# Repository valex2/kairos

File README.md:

# Kairos
The objective of this project was to develop a low-cost, portable AQI (Air Quality Index) monitor that logs key air quality metrics and stores them for long-term tracking.

This is driven by the worsening air quality due to climate change, particularly in regions like California where wildfires contribute to increased particulate matter in the atmosphere. Affordable sensors, such as Kairos, offer a scalable solution for monitoring air quality across large areas, providing national agencies with valuable data to analyze climate patterns, identify hotspots, and allocate resources more effectively.

A key advantage of Kairos is its portability and accessibility. Designed to be carried by individuals, it requires minimal infrastructure, reducing the overhead costs typically associated with large-scale environmental monitoring. This enables on-the-ground data collection and empowers individuals to better understand and respond to the air quality and environmental hazards in their immediate surroundings, while also meaningfully contributing to a larger, community or state-wide, AQI dataset. This version of Kairos serves as a proof of concept and has the following features:

1. Embedded compute
    1. The [**ATMEL SAMD51J19**](https://www.microchip.com/en-us/product/atsamd51j19a), an accessible chip, with 120MHz CPU, 256 KB RAM, and plenty of IO buses to handle sensor data and logging.
2. Instrumentation
    1. A [**Bosch SensorTech BME 688**](https://www.bosch-sensortec.com/products/environmental-sensors/gas-sensors/bme688/) — enabling high-accuracy pressure, humidity, temperature, Volatile Organic Compound (VOC) and Volatile Sulfur Compound (VSC) monitoring.
    2. An [**LTR-329ALS-01**](https://www.mouser.com/datasheet/2/239/Lite-On_LTR-329ALS-01%20DS_ver1.1-348647.pdf) — enabling visible- and IR-range light intensity measurements.
3. Communication modalities
    1. A **USB bus** — for communication with a host computer
    2. A **microSD** bus — for time-stamped ***logging*** of sensor values. Using an external SD card allows for prolonged operation without needing to pause logging
    3. A **display** — for on the go monitoring of sensor values
4. Two different power modes
    1. **USB Power** — embedded voltage regulators enable Kairos to be used in a stationary setting, say a roof of a building, for extended periods of time
    2. **Battery Power** — a 2500mAh LiPO and embedded charging circuitry allow Kairos to be taken on the go, for better-monitoring frequently travelled environments without requiring frequent charging.

While this version of Kairos demonstrates proof of concept, future iterations should expand its capabilities with the following features:

1. **UV Sensor**: To capture sun intensity across more (and more dangerous) wavelengths, providing a more comprehensive solar exposure assessment.
2. **GPS Module**: To enable precise tracking of Kairos’ location, facilitating the creation of accurate heatmaps for key AQI metrics.
3. **Bluetooth Syncing**: To allow seamless data transfer to mobile phones, removing the need to manually retrieve data from an SD card.
4. **A Centralized Server**: To aggregate data from multiple Kairos units, generating regional-level heatmaps and providing actionable insights from averaged data points across different areas.
5. **A rugged, waterproof, miniaturized shell for on the go use.**

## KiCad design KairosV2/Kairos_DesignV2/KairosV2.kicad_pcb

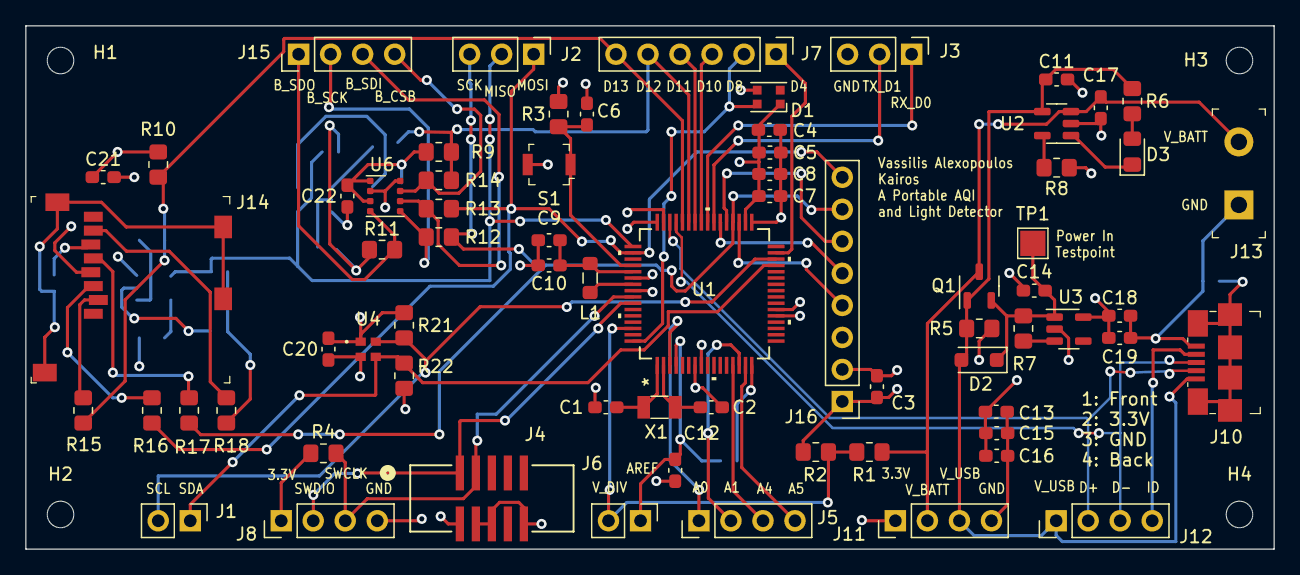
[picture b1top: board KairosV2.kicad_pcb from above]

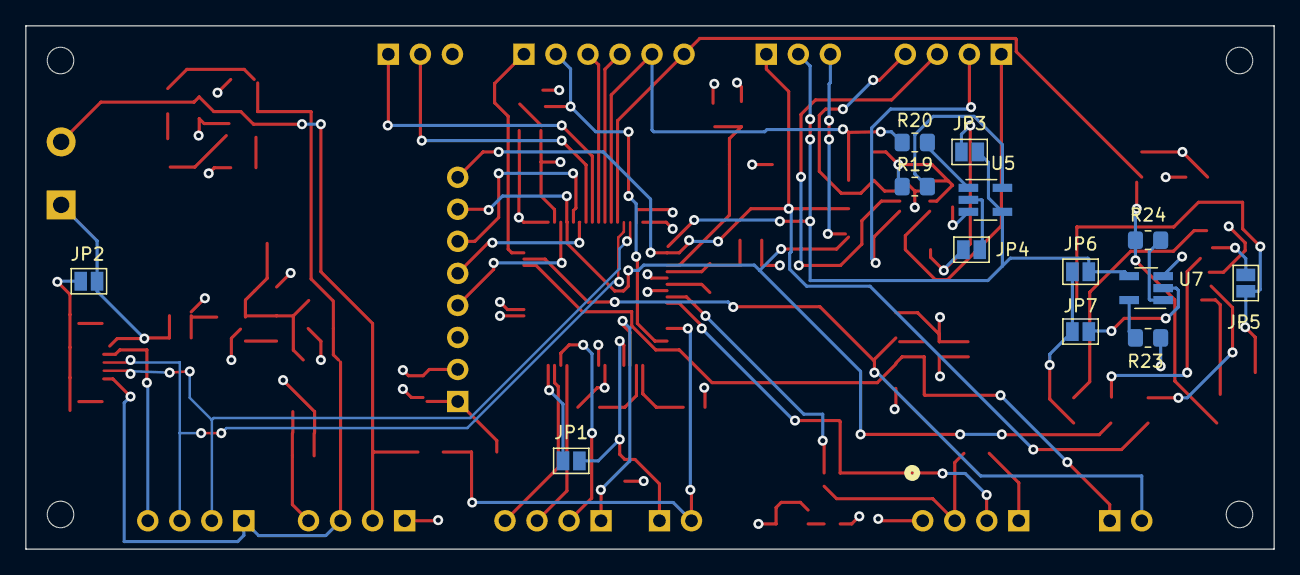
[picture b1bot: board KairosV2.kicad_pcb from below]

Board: 4 copper layers, 99.0 x 41.5 mm, 87 parts (13 on the bottom side), 59 nets.

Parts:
C1, C2: 22pF; C_0603_1608Metric_Pad1.08x0.95mm_HandSolder
C3, C4, C21, C22: 0.1u; C_0603_1608Metric_Pad1.08x0.95mm_HandSolder
C5, C6, C7, C9, C12, C15, C16, C19, C20: 1u; C_0603_1608Metric_Pad1.08x0.95mm_HandSolder
C8, C10, C13, C14, C18: 10u; C_0603_1608Metric_Pad1.08x0.95mm_HandSolder
C11, C17: 4.7u; C_0603_1608Metric_Pad1.08x0.95mm_HandSolder
D1: WS2812B; LED_WS2812B-2020_PLCC4_2.0x2.0mm
D2: Schottky; D_SOD-123F
D3: LED; LED_0805_2012Metric_Pad1.15x1.40mm_HandSolder
H1, H2, H3, H4: MountingHole; MountingHole_2.1mm
J1, J6: Conn_01x02; PinHeader_1x02_P2.54mm_Vertical
J2, J3: Conn_01x03; PinHeader_1x03_P2.54mm_Vertical
J4: 3221-10-0300-00; CONN10_3221-10-0300-00_CNC
J5, J8, J11, J12, J15: Conn_01x04; PinHeader_1x04_P2.54mm_Vertical
J7: Conn_01x06; PinHeader_1x06_P2.54mm_Vertical
J10: 10118192-0001LF; USB_Micro_B_Female_10118192
J13: 1935161; Terminal_Block_D1.3mm_P5mm
J14: 2908-05WB-MG; MicroSD_2908-05WB-MG
J16: Conn_01x08; PinHeader_1x08_P2.54mm_Vertical
JP1, JP2, JP3, JP4, JP5, JP6, JP7: SolderJumper_2_Open; SolderJumper-2_P1.3mm_Open_Pad1.0x1.5mm
L1: 31 Ohm at 100 MHz; L_0805_2012Metric_Pad1.05x1.20mm_HandSolder
Q1: DMG3415U-7; SOT-23-3
R1, R2, R5: 100k; R_0805_2012Metric_Pad1.20x1.40mm_HandSolder
R3, R4, R7: 10K; R_0805_2012Metric_Pad1.20x1.40mm_HandSolder
R6: 1K; R_0805_2012Metric_Pad1.20x1.40mm_HandSolder
R8: 2k; R_0805_2012Metric_Pad1.20x1.40mm_HandSolder
R9, R10, R21, R22: 3.3k; R_0805_2012Metric_Pad1.20x1.40mm_HandSolder
R11, R12, R13, R14, R19, R20, R23, R24: 0; R_0805_2012Metric_Pad1.20x1.40mm_HandSolder
R15, R16, R17, R18: 47k; R_0805_2012Metric_Pad1.20x1.40mm_HandSolder
S1: B3U-1000P; Switch_Tactile_SMD_B3U-1000P
TP1: Vin; TestPoint_Pad_2.0x2.0mm
U1: ATSAMD51J19A-AUT; TQFP64_PT_MCH
U2: MCP73831; SOT-23-5
U3: AP2112k-3.3V; SOT-23-5
U4: LTR-329ALS-01; LTR-329ALS-01_LTO
U5, U7: 74AHC1G125; SOT-23-5_HandSoldering
U6: BME688; Bosch_LGA-8_3x3mm_P0.8mm_ClockwisePinNumbering
X1: 32.768kHz; Crystal_SMD_3215-2Pin_3.2x1.5mm

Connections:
3.3V: C3.1, C4.1, C5.1, C7.1, C8.1, C13.1, C15.1, C16.1, C18.1, C19.1, C20.1, C21.1, C22.1, D1.1 (VDD), J4.1, J8.1, J11.1, J14.4 (VDD), J16.2, JP1.1 (A), R3.2, R4.2, R9.1, R10.1, R19.2, R21.1, R22.1, R23.2, U1.8 (VDDANA), U1.16 (PA07), U1.21 (VDDIOB), U1.34 (VDDIO), U1.48 (VDDIO), U1.56 (VDDIO), U3.5 (OUT), U4.1 (VDD), U6.6 (VDDIO), U6.8 (VDD)
A0: J5.1, U1.3 (PA02)
A1: J5.2, U1.14 (PA05)
A4: J5.3, U1.13 (PA04)
A5: J5.4, U1.15 (PA06)
AREF: C12.1, J6.1, JP1.2 (B), U1.4 (PA03)
BME_CSB: J15.4, R14.2, U6.2 (CSB)
BME_MISO: JP3.1 (A), JP4.1 (A), R11.1
BME_SCK: J15.2, R12.2, U6.4 (SCK)
BME_SDI: J15.3, R13.2, U6.3 (SDI)
BME_SDO: J15.1, R11.2, U6.5 (SDO)
D4: J7.1, U1.31 (PA14)
D5: J16.4, U1.35 (PA16)
D6: J16.6, U1.37 (PA18)
D8_Pix: D1.4 (DIN), J7.2, U1.64 (PB03)
D9: J16.5, U1.38 (PA19)
D10: J7.3, U1.41 (PA20)
D11: J7.4, U1.42 (PA21)
D12: J7.5, R9.2, R14.1, R20.2, U1.43 (PA22)
D13: J7.6, R10.2, R15.1, R24.2, U1.44 (PA23)
D+: J10.2, J12.2, U1.46 (PA25)
D-: J10.3, J12.3, U1.45 (PA24)
GND: C1.1, C2.1, C3.2, C4.2, C5.2, C6.2, C7.2, C8.2, C9.2, C10.2, C11.2, C12.2, C13.2, C14.2, C15.2, C16.2, C17.2, C18.2, C19.2, C20.2, C21.2, C22.2, D1.3 (VSS), J3.3, J4.3, J4.5, J4.9, J8.4, J10.5, J11.4, J13.1, J14.6 (GND), J16.1, JP2.2 (B), JP5.1 (A), R2.1, R5.1, R8.1, S1.2, U1.7 (GNDANA), U1.22 (GND), U1.33 (GND), U1.47 (GND), U1.54 (GND), U2.2 (VSS), U3.2 (GND), U4.2 (GND), U5.3 (GND), U6.1 (GND), U6.7 (GND), U7.3 (GND)
ID: J10.4, J12.4
MISO: J2.2, JP3.2 (B), JP6.2 (B), U1.49 (PB22), U5.4, U7.4
MOSI: J2.1, J16.8, R13.1, R16.1, U1.50 (PB23)
unnamed: D3.2 (A), R6.2
unnamed: D3.1 (K), U2.1 (STAT)
unnamed: J14.2 (CS), R15.2
unnamed: J14.3 (DATA_IN), R16.2
unnamed: J14.7 (DATA_OUT), R18.2
unnamed: J14.5 (SCLK), R17.2
unnamed: J14.9 (SHLD), JP5.2 (B)
unnamed: J10.SH, JP2.1 (A)
unnamed: JP4.2 (B), U5.2
unnamed: JP7.2 (B), U7.2
unnamed: C14.1, D2.1, Q1.2 (S), R7.2, TP1.1, U3.1 (IN)
unnamed: R20.1, U5.1
unnamed: R24.1, U7.1
unnamed: C1.2, U1.1 (PA00), X1.1
unnamed: C2.2, U1.2 (PA01), X1.2
unnamed: C9.1, C10.1, L1.1, U1.53 (VDDCORE)
unnamed: L1.2, U1.55 (VSW)
unnamed: R8.2, U2.5 (PROG)
unnamed: R7.1, U3.3 (EN)
unnamed: R19.1, U5.5 (VCC)
unnamed: R23.1, U7.5 (VCC)
RX_D0: J3.1, U1.40 (PB17)
SCK: J2.3, J16.7, R12.1, R17.1, U1.36 (PA17)
SCL: J1.2, R21.2, U1.30 (PA13), U4.4 (SCL)
SDA: J1.1, R22.2, U1.29 (PA12), U4.3 (SDA)
SD_MISO: JP6.1 (A), JP7.1 (A), R18.1
SWCLK: J4.4, J8.3, R4.1, U1.57 (PA30)
SWDIO: J4.2, J8.2, U1.58 (PA31)
TX_D1: J3.2, U1.39 (PB16)
V_BATT: C17.1, J11.2, J13.2, Q1.3 (D), R1.2, U2.3 (VBAT)
V_DIV: J6.2, R1.1, R2.2, U1.62 (PB01)
V_USB: C11.1, D2.2, J10.1, J11.3, J12.1, Q1.1 (G), R5.2, R6.1, U2.4 (VIN)
~RESET: C6.1, R3.1, S1.1, U1.52 (RESETN)

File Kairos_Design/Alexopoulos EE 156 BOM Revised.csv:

#,Reference,Qty (New),Value,Footprint,DNP,Supplier 1,Supplier 1 S/N,MFR,MFR S/N
1,BOM1,6,10uH 0805,,,https://www.digikey.com/en/products/detail/taiyo-yuden/LBR20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,587-2045-1-ND,Taiyo Yuden,LBR2012T100K
2,BOM2,20,0 Ohm Jumper,,,https://www.digikey.com/en/products/detail/stackpole-electro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,RMCF0805ZT0R00CT-ND,Stackpole Electronics Inc,RMCF0805ZT0R00
3,BOM3,16,10kO 0805,,,https://www.digikey.com/en/products/detail/stackpole-electro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,RMCF0805JT10K0CT-ND,Stackpole Electronics Inc,RMCF0805JT10K0
4,BOM4,6,20pF 0603,,,https://www.digikey.com/en/products/detail/samsung-electro-m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,1276-1187-1-ND,Samsung Electro-Mechanics,CL10C200JB8NNNC
5,BOM5,6,24pF 0603,,,https://www.digikey.com/en/products/detail/murata-electronic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,490-1412-1-ND,Murata Electronics,GRM1885C1H240JA01D
6,BOM6,1,LiPo 3.7V 2.5AH,,,https://www.adafruit.com/product/328,328,,
7,BOM7,1,OLED Display,,,https://www.digikey.com/en/products/detail/adafruit-industri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,1528-1512-ND,Adafruit Industries LLC,938
8,BOM8,6,Header Pins,,,https://www.digikey.com/en/products/detail/adam-tech/PH1-09-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,2057-PH1-09-UA-ND,Adam Tech,PH1-09-UA
9,"C1, C2",8,22pF,Capacitor_SMD:C_0603_1608Metric_Pad1.08x0.95mm_HandSolder,,https://www.digikey.com/en/products/detail/kemet/C0603C220J5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,399-C0603C220J5GAC7867CT-ND,KEMET,C0603C220J5GAC7867
10,"C3, C4, C21, C22",16,0.1u,Capacitor_SMD:C_0603_1608Metric_Pad1.08x0.95mm_HandSolder,,https://www.digikey.com/en/products/detail/yageo/CC0603KRX7R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,311-1088-1-ND,YAGEO,CC0603KRX7R7BB104
11,"C5, C6, C7, C9, C12, C15, C16, C19, C20",36,1u,Capacitor_SMD:C_0603_1608Metric_Pad1.08x0.95mm_HandSolder,,https://www.digikey.com/en/products/detail/yageo/CC0603KRX7R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,311-1446-1-ND,YAGEO,CC0603KRX7R7BB105
12,"C8, C10, C13, C14, C18",20,10u,Capacitor_SMD:C_0603_1608Metric_Pad1.08x0.95mm_HandSolder,,https://www.digikey.com/en/products/detail/taiyo-yuden/JMK10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,587-5869-1-ND,Taiyo Yuden,JMK107ABJ106MA-T
13,"C11, C17",8,4.7u,Capacitor_SMD:C_0603_1608Metric_Pad1.08x0.95mm_HandSolder,,https://www.digikey.com/en/products/detail/samsung-electro-m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,1276-1044-1-ND,Samsung Electro-Mechanics,CL10A475KP8NNNC
14,D1,1,WS2812B,LED_SMD:LED_WS2812B-2020_PLCC4_2.0x2.0mm,,https://www.adafruit.com/product/4684,WS2812B,Adafruit,
15,D2,3,Schottky,Diode_SMD:D_SOD-123F,,https://www.digikey.com/en/products/detail/onsemi/MBR120LSFT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,MBR120LSFT1GOSCT-ND,onsemi,MBR120LSFT1G
16,D3,3,LED,LED_SMD:LED_0805_2012Metric_Pad1.15x1.40mm_HandSolder,,https://www.digikey.com/en/products/detail/qt-brightek-qtb/Q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,1516-1084-1-ND,QT Brightek (QTB),QBLP631-IG
20,J4,2,3221-10-0300-00,Connector:CONN10_3221-10-0300-00_CNC,,https://www.digikey.com/en/products/detail/cnc-tech/3221-10-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,1175-1735-ND,CNC Tech,3221-10-0300-00
23,J10,3,10118192-0001LF,digikey-footprints:USB_Micro_B_Female_10118192,,https://www.digikey.com/en/products/detail/amphenol-icc-fci/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,609-4613-1-ND,Amphenol ICC (FCI),10118192-0001LF
24,J13,3,1935161,digikey-footprints:Terminal_Block_D1.3mm_P5mm,,https://www.digikey.com/en/products/detail/phoenix-contact/1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,277-1667-ND,Phoenix Contact,1935161
25,J14,3,2908-05WB-MG,digikey-footprints:MicroSD_2908-05WB-MG,,https://www.digikey.com/en/products/detail/3m/2908-05WB-MG/1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,3M5607CT-ND,3M,2908-05WB-MG
29,L1,4,31 Ohm at 100 MHz,Inductor_SMD:L_0805_2012Metric_Pad1.05x1.20mm_HandSolder,,https://www.digikey.com/en/products/detail/laird-signal-inte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,240-2394-1-ND,Laird-Signal Integrity Products,HI0805Q310R-10
30,Q1,4,DMG3415U-7,Package_TO_SOT_SMD:SOT-23-3,,https://www.digikey.com/en/products/detail/diodes-incorporat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,DMG3415UDICT-ND,Diodes Incorporated,DMG3415U-7
31,"R1, R2, R5",12,100k,Resistor_SMD:R_0805_2012Metric_Pad1.20x1.40mm_HandSolder,,https://www.digikey.com/en/products/detail/yageo/RC0805FR-07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,311-100KCRCT-ND,YAGEO,RC0805FR-07100KL
32,"R3, R4, R7",12,10K,Resistor_SMD:R_0805_2012Metric_Pad1.20x1.40mm_HandSolder,,https://www.digikey.com/en/products/detail/stackpole-electro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,RMCF0805JT10K0CT-ND,Stackpole Electronics Inc,RMCF0805JT10K0
33,R6,4,1K,Resistor_SMD:R_0805_2012Metric_Pad1.20x1.40mm_HandSolder,,https://www.digikey.com/en/products/detail/yageo/RC0805FR-07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,311-1.00KCRCT-ND,YAGEO,RC0805FR-071KL
34,R8,4,2k,Resistor_SMD:R_0805_2012Metric_Pad1.20x1.40mm_HandSolder,,https://www.digikey.com/en/products/detail/panasonic-electro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,P2.00KCCT-ND,Panasonic Electronic Components,ERJ-6ENF2001V
35,"R9, R10, R21, R22",16,3.3k,Resistor_SMD:R_0805_2012Metric_Pad1.20x1.40mm_HandSolder,,https://www.digikey.com/en/products/detail/stackpole-electro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,RMCF0805JT3K30CT-ND,Stackpole Electronics Inc,RMCF0805JT3K30
36,"R11, R12, R13, R14, R19, R20, R23, R24",32,0,Resistor_SMD:R_0805_2012Metric_Pad1.20x1.40mm_HandSolder,,https://www.digikey.com/en/products/detail/stackpole-electro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,RMCF0805ZT0R00CT-ND,Stackpole Electronics Inc,RMCF0805ZT0R00
37,"R15, R16, R17, R18",16,47k,Resistor_SMD:R_0805_2012Metric_Pad1.20x1.40mm_HandSolder,,https://www.digikey.com/en/products/detail/stackpole-electro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,RMCF0805JT47K0CT-ND,Stackpole Electronics Inc,RMCF0805JT47K0
38,S1,4,B3U-1000P,digikey-footprints:Switch_Tactile_SMD_B3U-1000P,,https://www.digikey.com/en/products/detail/omron-electronics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,SW1020CT-ND,Omron Electronics Inc-EMC Div,B3U-1000P
40,U1,3,ATSAMD51J19A-AUT,SAMD51J19A-AUT:TQFP64_PT_MCH,,https://www.digikey.com/en/products/detail/microchip-technol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,ATSAMD51J19A-AUTCT-ND,Microchip Technology,ATSAMD51J19A-AUT
41,U2,3,MCP73831,Package_TO_SOT_SMD:SOT-23-5,,https://www.digikey.com/en/products/detail/microchip-technol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,MCP73831T-2ACI/OTCT-ND,Microchip Technology,MCP73831T-2ACI/OT
42,U3,3,AP2112k-3.3V,Package_TO_SOT_SMD:SOT-23-5,,https://www.digikey.com/en/products/detail/diodes-incorporat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,AP2112K-3.3TRG1DICT-ND,Diodes Incorporated,AP2112K-3.3TRG1
43,U4,3,LTR-329ALS-01,LTR329:LTR-329ALS-01_LTO,,https://www.digikey.com/en/products/detail/liteon/LTR-329ALS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,160-2160-1-ND,Lite-On Inc.,LTR-329ALS-01
44,"U5, U7",6,74AHC1G125,Package_TO_SOT_SMD:SOT-23-5_HandSoldering,,https://www.digikey.com/en/products/detail/texas-instruments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,296-8744-1-ND,Texas Instruments,SN74AHC1G125DBVR
45,U6,3,BME688,Package_LGA:Bosch_LGA-8_3x3mm_P0.8mm_ClockwisePinNumbering,,https://www.digikey.com/en/products/detail/bosch-sensortec/B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,828-BME688CT-ND,Bosch Sensortec,BME688
46,X1,4,32.768kHz,Crystal:Crystal_SMD_3215-2Pin_3.2x1.5mm,,https://www.digikey.com/en/products/detail/hosonic-electroni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,3186-ETST00327000JECT-ND,"Hosonic Electronic Co., Ltd",ETST00327000JE

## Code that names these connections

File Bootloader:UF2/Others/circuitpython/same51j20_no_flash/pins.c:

#include "shared-bindings/board/__init__.h"

STATIC const mp_rom_map_elem_t board_module_globals_table[] = {
    CIRCUITPYTHON_BOARD_DICT_STANDARD_ITEMS

    { MP_ROM_QSTR(MP_QSTR_IsoNegAnalogIn), MP_ROM_PTR(&pin_PA02) },
    
    { MP_ROM_QSTR(MP_QSTR_VREF), MP_ROM_PTR(&pin_PA03) },

    { MP_ROM_QSTR(MP_QSTR_A0), MP_ROM_PTR(&pin_PA04) },

    { MP_ROM_QSTR(MP_QSTR_IsoPosAnalogIn), MP_ROM_PTR(&pin_PA05) },
    
    { MP_ROM_QSTR(MP_QSTR_A1), MP_ROM_PTR(&pin_PA06) },
  
    { MP_ROM_QSTR(MP_QSTR_SDA), MP_ROM_PTR(&pin_PA12) },
   
    { MP_ROM_QSTR(MP_QSTR_SCL), MP_ROM_PTR(&pin_PA13) },

    { MP_ROM_QSTR(MP_QSTR_DO1), MP_ROM_PTR(&pin_PA14) },
 
    { MP_ROM_QSTR(MP_QSTR_DO2), MP_ROM_PTR(&pin_PA16) },
  
    { MP_ROM_QSTR(MP_QSTR_SCK), MP_ROM_PTR(&pin_PA17) },

    { MP_ROM_QSTR(MP_QSTR_RelayNeg), MP_ROM_PTR(&pin_PA18) },

    { MP_ROM_QSTR(MP_QSTR_RelayPos), MP_ROM_PTR(&pin_PA19) },

    { MP_ROM_QSTR(MP_QSTR_D0), MP_ROM_PTR(&pin_PA20) },

    { MP_ROM_QSTR(MP_QSTR_D1), MP_ROM_PTR(&pin_PA21) },

    { MP_ROM_QSTR(MP_QSTR_D2), MP_ROM_PTR(&pin_PA22) },

    { MP_ROM_QSTR(MP_QSTR_D3), MP_ROM_PTR(&pin_PA23) },

    { MP_ROM_QSTR(MP_QSTR_BatteryMonitor), MP_ROM_PTR(&pin_PB00) },

    { MP_ROM_QSTR(MP_QSTR_NeoPWR), MP_ROM_PTR(&pin_PB02) },
   
    { MP_ROM_QSTR(MP_QSTR_NEOPIXEL), MP_ROM_PTR(&pin_PB03) },

    { MP_ROM_QSTR(MP_QSTR_HVmeasurementAnalogIn), MP_ROM_PTR(&pin_PB08) },

    { MP_ROM_QSTR(MP_QSTR_A2), MP_ROM_PTR(&pin_PB09) },

    { MP_ROM_QSTR(MP_QSTR_BoostEnableOut), MP_ROM_PTR(&pin_PB13) },
    
    { MP_ROM_QSTR(MP_QSTR_TXD5), MP_ROM_PTR(&pin_PB16) },

    { MP_ROM_QSTR(MP_QSTR_RXD6), MP_ROM_PTR(&pin_PB17) },

    { MP_ROM_QSTR(MP_QSTR_MISO), MP_ROM_PTR(&pin_PB22) },
 
    { MP_ROM_QSTR(MP_QSTR_MOSI), MP_ROM_PTR(&pin_PB23) },

    { MP_ROM_QSTR(MP_QSTR_CANTX), MP_ROM_PTR(&pin_PB14) },
    { MP_ROM_QSTR(MP_QSTR_CANRX), MP_ROM_PTR(&pin_PB15) },
    { MP_ROM_QSTR(MP_QSTR_CANS), MP_ROM_PTR(&pin_PB12) },


    { MP_ROM_QSTR(MP_QSTR_I2C), MP_ROM_PTR(&board_i2c_obj) },
    { MP_ROM_QSTR(MP_QSTR_SPI), MP_ROM_PTR(&board_spi_obj) },
    { MP_ROM_QSTR(MP_QSTR_UART), MP_ROM_PTR(&board_uart_obj) },
};
MP_DEFINE_CONST_DICT(board_module_globals, board_module_globals_table);

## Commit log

2024-09-08 update display, fixed SD card
2024-09-08 adding plotting function
2024-09-08 SD card working
2024-09-09 bootloader and uf2 addition
2024-09-09 update code.py and plotting function for gas
2024-09-09 adding pics
2024-09-09 big data
2024-09-09 report and boards
2024-09-09 restructuring
2024-12-25 syncing
2024-12-25 beginnning v2
2024-12-25 beginning v2
